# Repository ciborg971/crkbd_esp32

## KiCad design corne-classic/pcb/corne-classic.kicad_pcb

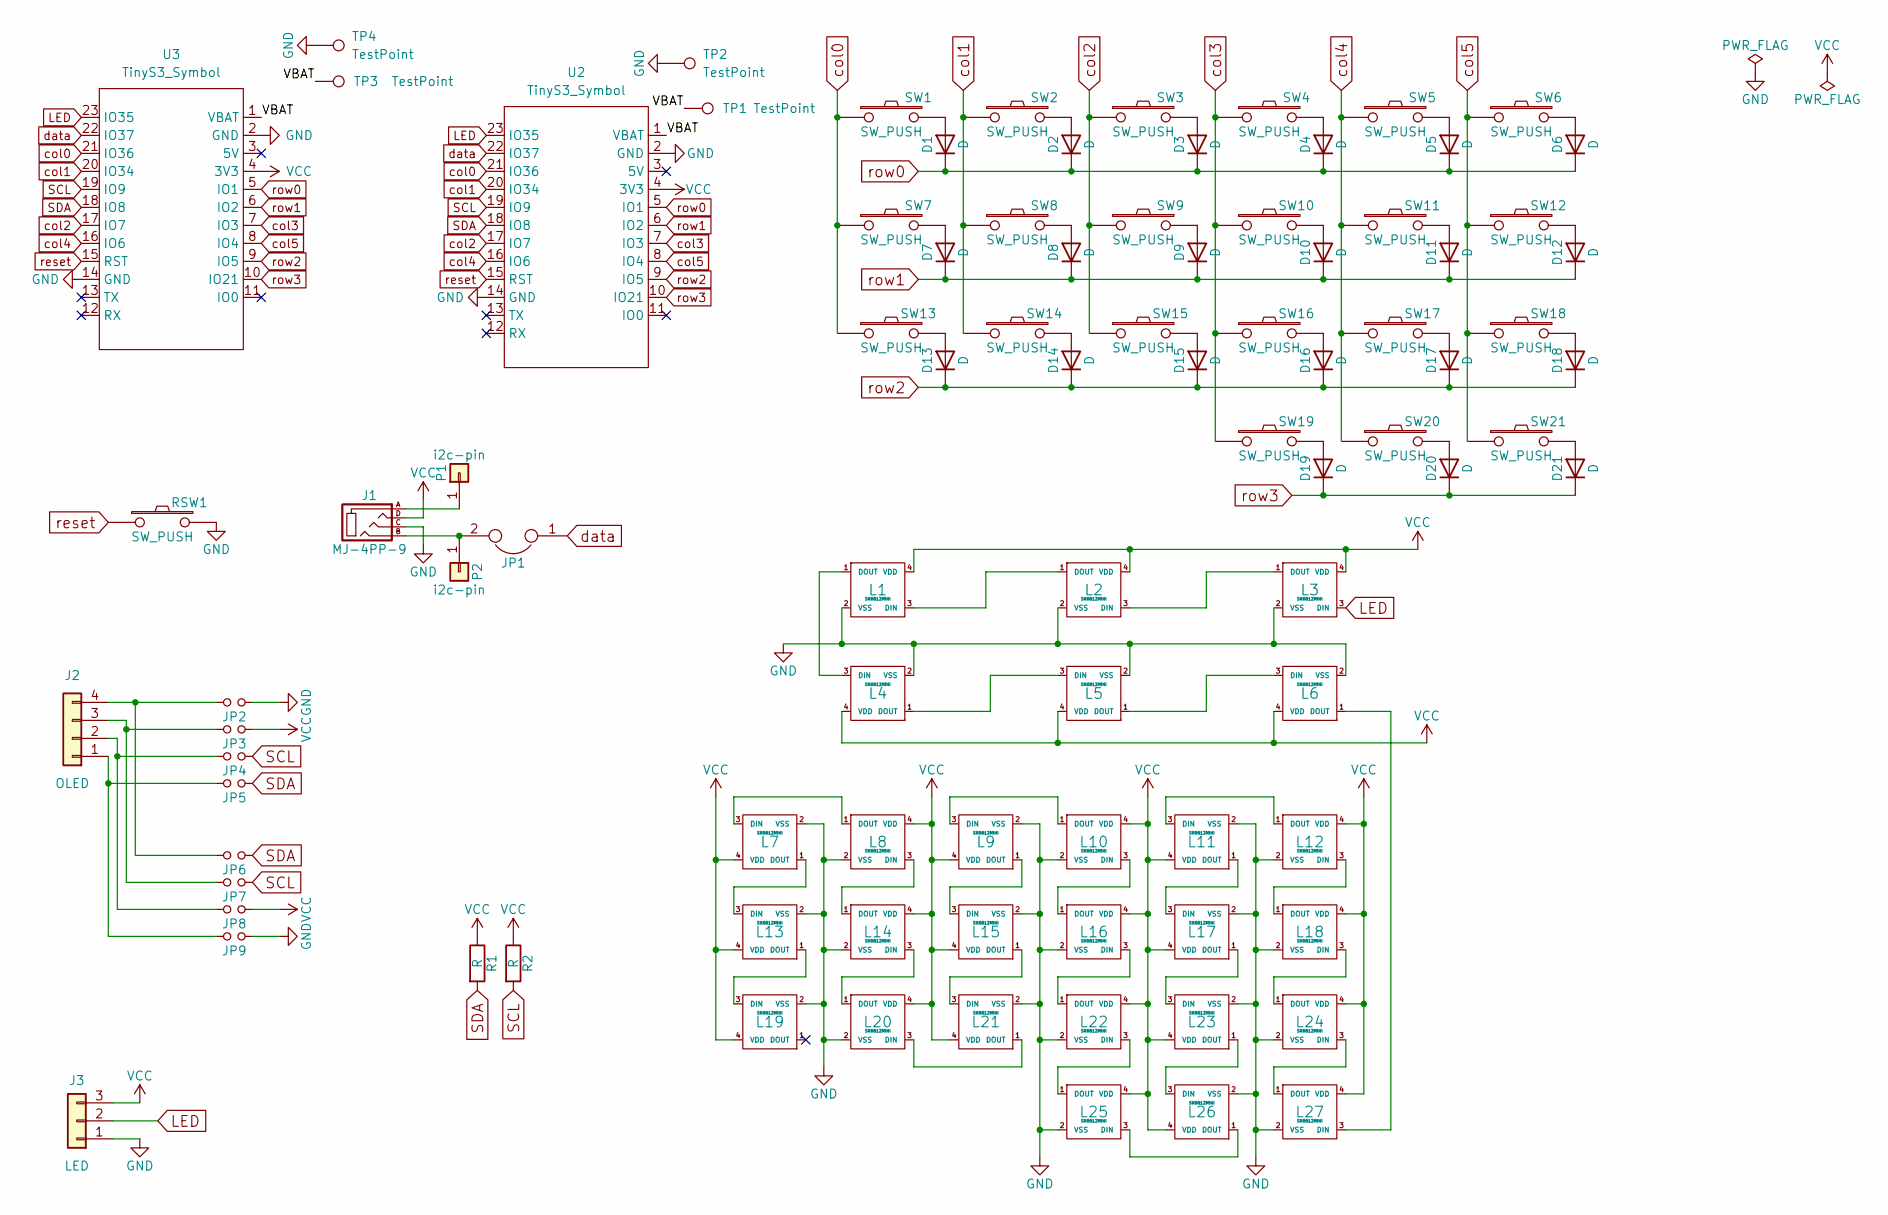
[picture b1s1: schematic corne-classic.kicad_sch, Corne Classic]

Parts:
D1, D2, D3, D4, D5, D6, D7, D8, D9, D10, D11, D12, D13, D14, D15, D16, D17, D18, D19, D20, D21: D; D3_TH_SMD
J1: MJ-4PP-9
J2: OLED
J3: LED; StripLED_rev
JP1: JP
JP2, JP3, JP4, JP5, JP6, JP7, JP8, JP9: Jumper
L1, L2, L3, L4, L5, L6: SK6812MINI; SK6812MINI_underglow
L7, L8, L9, L10, L11, L12, L13, L14, L15, L16, L17, L18, L19, L20, L21, L22, L23, L24, L25, L26, L27: SK6812MINI; SK6812MINI_rev
P1, P2: i2c-pin; 1pin_conn
R1, R2: R
RSW1: SW_PUSH; ResetSW
SW1, SW2, SW3, SW4, SW5, SW6, SW7, SW8, SW9, SW10, SW11, SW12, SW13, SW14, SW15, SW16, SW17, SW18, SW19, SW20: SW_PUSH; MX_ALPS_PG1350_noLed
SW21: SW_PUSH; MX_ALPS_PG1350_noLed_1.75u
TP1, TP2, TP3, TP4: TestPoint; TestPoint_Pad_D1.5mm
U2, U3: TinyS3_Symbol; TinyS3

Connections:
/VBAT: TP1.1, TP3.1, U2.1 (VBAT), U3.1 (VBAT)
GND: J1.C, J3.1, JP2.1, JP9.1, L1.2 (VSS), L2.2 (VSS), L3.2 (VSS), L4.2 (VSS), L5.2 (VSS), L6.2 (VSS), L7.2 (VSS), L8.2 (VSS), L9.2 (VSS), L10.2 (VSS), L11.2 (VSS), L12.2 (VSS), L13.2 (VSS), L14.2 (VSS), L15.2 (VSS), L16.2 (VSS), L17.2 (VSS), L18.2 (VSS), L19.2 (VSS), L20.2 (VSS), L21.2 (VSS), L22.2 (VSS), L23.2 (VSS), L24.2 (VSS), L25.2 (VSS), L26.2 (VSS), L27.2 (VSS), RSW1.2, TP2.1, TP4.1, U2.2 (GND), U2.14 (GND), U3.2 (GND), U3.14 (GND)
LED: J3.2, L3.3 (DIN), U2.23 (IO35), U3.23 (IO35)
unnamed: D1.2 (A), SW1.2
unnamed: D2.2 (A), SW2.2
unnamed: D3.2 (A), SW3.2
unnamed: D4.2 (A), SW4.2
unnamed: D5.2 (A), SW5.2
unnamed: D6.2 (A), SW6.2
unnamed: D7.2 (A), SW7.2
unnamed: D8.2 (A), SW8.2
unnamed: D9.2 (A), SW9.2
unnamed: D10.2 (A), SW10.2
unnamed: D11.2 (A), SW11.2
unnamed: D12.2 (A), SW12.2
unnamed: D13.2 (A), SW13.2
unnamed: D14.2 (A), SW14.2
unnamed: D15.2 (A), SW15.2
unnamed: D16.2 (A), SW16.2
unnamed: D17.2 (A), SW17.2
unnamed: D18.2 (A), SW18.2
unnamed: D19.2 (A), SW19.2
unnamed: D20.2 (A), SW20.2
unnamed: D21.2 (A), SW21.2
unnamed: J2.1, JP5.2, JP9.2
unnamed: J2.2, JP4.2, JP8.2
unnamed: J2.3, JP3.2, JP7.2
unnamed: J2.4, JP2.2, JP6.2
unnamed: L7.3 (DIN), L8.1 (DOUT)
unnamed: L10.3 (DIN), L16.1 (DOUT)
unnamed: L9.3 (DIN), L10.1 (DOUT)
unnamed: L11.3 (DIN), L12.1 (DOUT)
unnamed: L11.1 (DOUT), L17.3 (DIN)
unnamed: L12.3 (DIN), L18.1 (DOUT)
unnamed: L7.1 (DOUT), L13.3 (DIN)
unnamed: L13.1 (DOUT), L19.3 (DIN)
unnamed: L14.3 (DIN), L20.1 (DOUT)
unnamed: L8.3 (DIN), L14.1 (DOUT)
unnamed: L9.1 (DOUT), L15.3 (DIN)
unnamed: L15.1 (DOUT), L21.3 (DIN)
unnamed: L16.3 (DIN), L22.1 (DOUT)
unnamed: L17.1 (DOUT), L23.3 (DIN)
unnamed: L18.3 (DIN), L24.1 (DOUT)
unnamed: L20.3 (DIN), L21.1 (DOUT)
unnamed: L22.3 (DIN), L25.1 (DOUT)
unnamed: L1.1 (DOUT), L4.3 (DIN)
unnamed: L1.3 (DIN), L2.1 (DOUT)
unnamed: L23.1 (DOUT), L26.3 (DIN)
unnamed: L2.3 (DIN), L3.1 (DOUT)
unnamed: L24.3 (DIN), L27.1 (DOUT)
unnamed: L25.3 (DIN), L26.1 (DOUT)
unnamed: L4.1 (DOUT), L5.3 (DIN)
unnamed: L5.1 (DOUT), L6.3 (DIN)
unnamed: J1.A, P1.1
SCL: JP4.1, JP7.1, R2.2, U2.19 (IO9), U3.19 (IO9)
SDA: JP5.1, JP6.1, R1.2, U2.18 (IO8), U3.18 (IO8)
VCC: J1.D, J3.3, JP3.1, JP8.1, L1.4 (VDD), L2.4 (VDD), L3.4 (VDD), L4.4 (VDD), L5.4 (VDD), L6.4 (VDD), L7.4 (VDD), L8.4 (VDD), L9.4 (VDD), L10.4 (VDD), L11.4 (VDD), L12.4 (VDD), L13.4 (VDD), L14.4 (VDD), L15.4 (VDD), L16.4 (VDD), L17.4 (VDD), L18.4 (VDD), L19.4 (VDD), L20.4 (VDD), L21.4 (VDD), L22.4 (VDD), L23.4 (VDD), L24.4 (VDD), L25.4 (VDD), L26.4 (VDD), L27.4 (VDD), R1.1, R2.1, U2.4 (3V3), U3.4 (3V3)
col0: SW1.1, SW7.1, SW13.1, U2.21 (IO36), U3.21 (IO36)
col1: SW2.1, SW8.1, SW14.1, U2.20 (IO34), U3.20 (IO34)
col2: SW3.1, SW9.1, SW15.1, U2.17 (IO7), U3.17 (IO7)
col3: SW4.1, SW10.1, SW16.1, SW19.1, U2.7 (IO3), U3.7 (IO3)
col4: SW5.1, SW11.1, SW17.1, SW20.1, U2.16 (IO6), U3.16 (IO6)
col5: SW6.1, SW12.1, SW18.1, SW21.1, U2.8 (IO4), U3.8 (IO4)
data: JP1.1, U2.22 (IO37), U3.22 (IO37)
reset: RSW1.1, U2.15 (RST), U3.15 (RST)
row0: D1.1 (K), D2.1 (K), D3.1 (K), D4.1 (K), D5.1 (K), D6.1 (K), U2.5 (IO1), U3.5 (IO1)
row1: D7.1 (K), D8.1 (K), D9.1 (K), D10.1 (K), D11.1 (K), D12.1 (K), U2.6 (IO2), U3.6 (IO2)
row2: D13.1 (K), D14.1 (K), D15.1 (K), D16.1 (K), D17.1 (K), D18.1 (K), U2.9 (IO5), U3.9 (IO5)
row3: D19.1 (K), D20.1 (K), D21.1 (K), U2.10 (IO21), U3.10 (IO21)

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
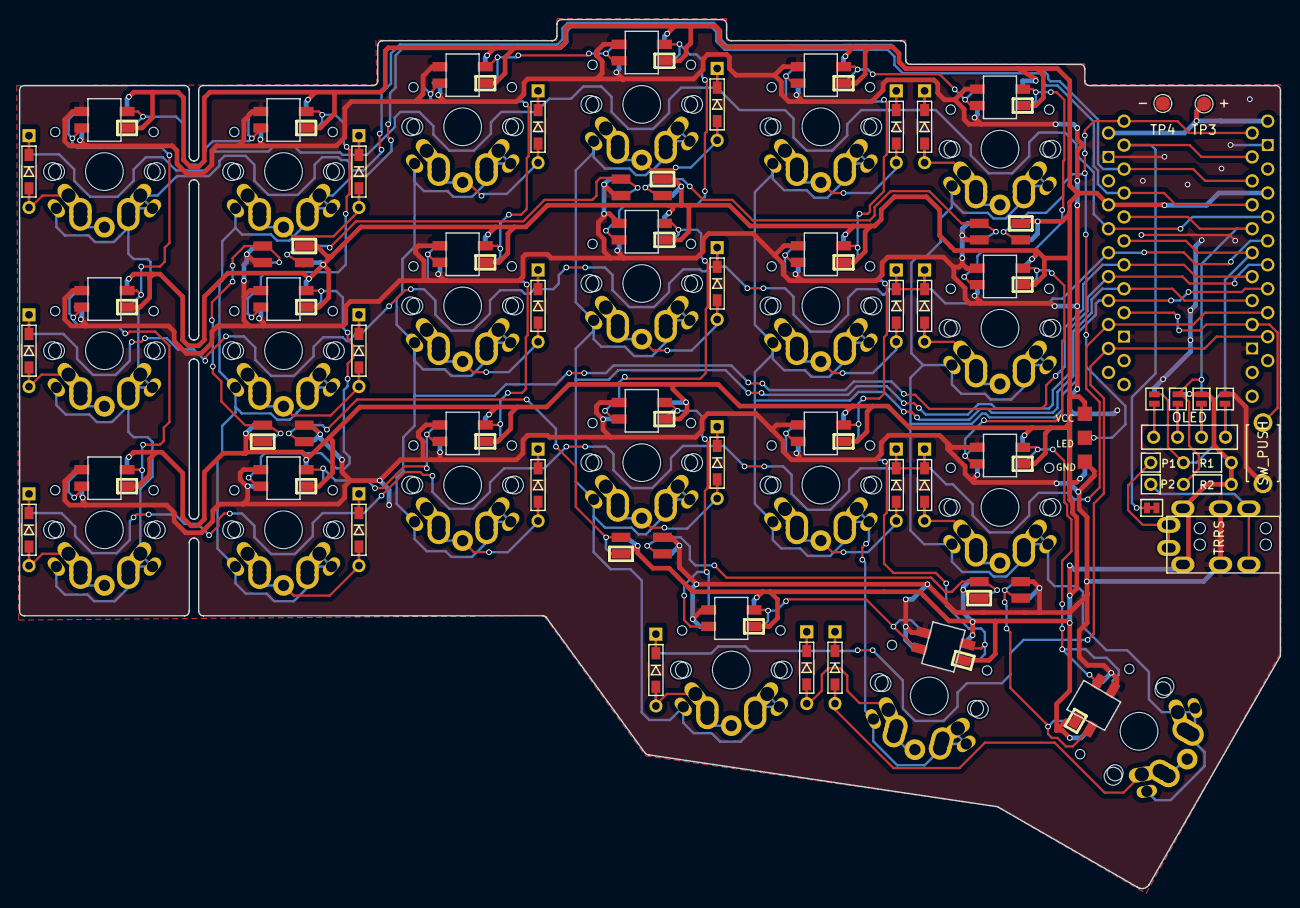
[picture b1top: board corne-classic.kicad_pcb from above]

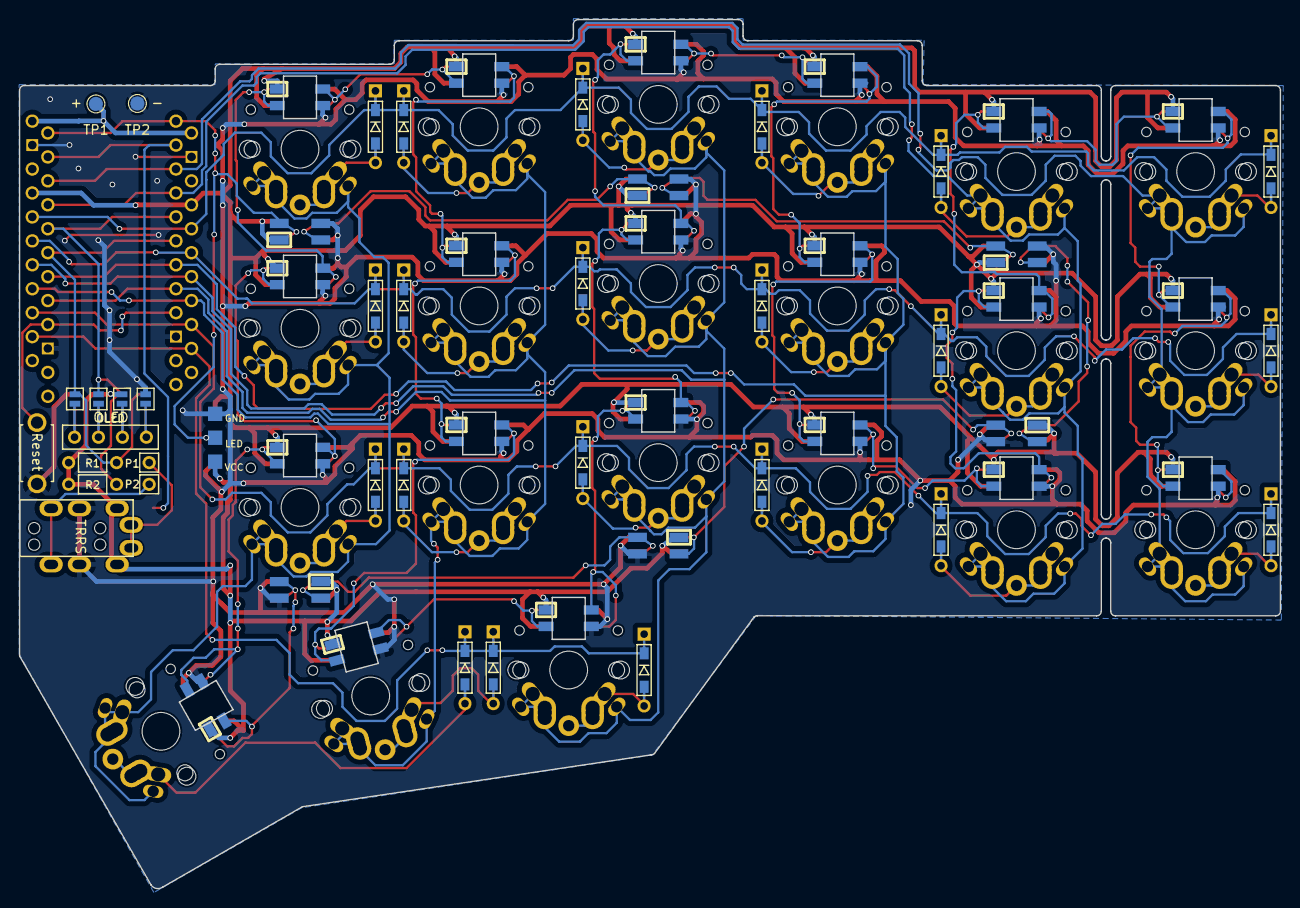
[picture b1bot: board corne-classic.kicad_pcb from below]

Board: 2 copper layers, 133.8 x 92.2 mm, 92 parts (7 on the bottom side), 70 nets.

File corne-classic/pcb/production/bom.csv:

Designator,Footprint,Quantity,Value,LCSC Part #
"D1, D10, D11, D12, D13, D14, D15, D16, D17, D18, D19, D2, D20, D21, D3, D4, D5, D6, D7, D8, D9",D3_TH_SMD,21,D,
J1,MJ-4PP-9,1,MJ-4PP-9,
J2,OLED,1,OLED,
J3,StripLED_rev,1,LED,
JP1,JPC2,1, ,
"JP2, JP3, JP4, JP5, JP6, JP7, JP8, JP9",Jumper,8, ,
"L1, L2, L3, L4, L5, L6",SK6812MINI_underglow_rev,6,SK6812MINI,
"L10, L11, L12, L13, L14, L15, L16, L17, L18, L19, L20, L21, L22, L23, L24, L25, L26, L27, L7, L8, L9",SK6812MINI_rev,21,SK6812MINI,
"P1, P2",1pin_conn,2,i2c-pin,
"R1, R2",R,2,R,
RSW1,ResetSW,1,SW_PUSH,
"SW1, SW10, SW11, SW12, SW13, SW14, SW15, SW16, SW17, SW18, SW19, SW2, SW20, SW3, SW4, SW5, SW6, SW7, SW8, SW9",MX_ALPS_PG1350_noLed,20,SW_PUSH,
SW21,MX_ALPS_PG1350_noLed_1.75u,1,SW_PUSH,
"TP1, TP2, TP3, TP4",TestPoint_Pad_D1.5mm,4,TestPoint,
"U2, U3",TinyS3,2,TinyS3_Symbol,

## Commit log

2024-03-31 Replaced Arduino by Esp32 TinyS3. Got a crash while rooting ...
2024-04-01 routing + prod files
